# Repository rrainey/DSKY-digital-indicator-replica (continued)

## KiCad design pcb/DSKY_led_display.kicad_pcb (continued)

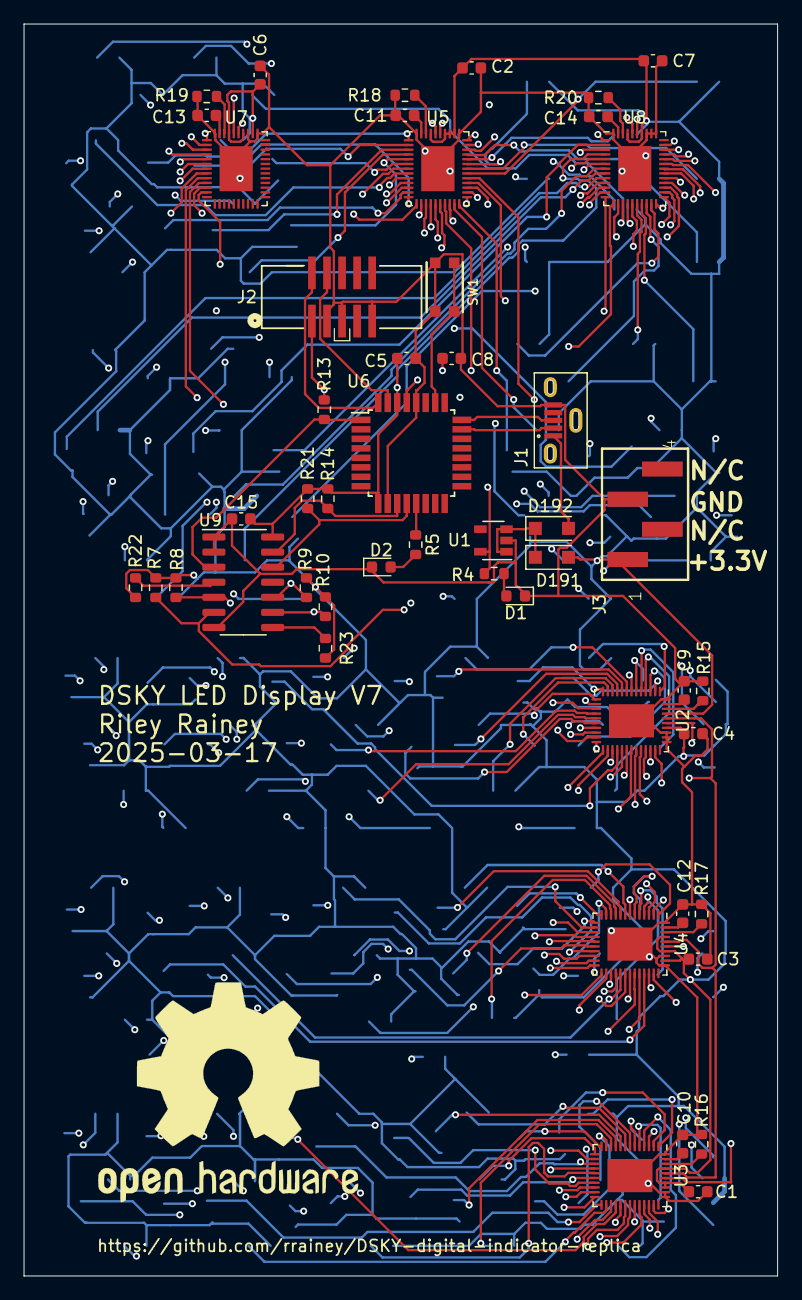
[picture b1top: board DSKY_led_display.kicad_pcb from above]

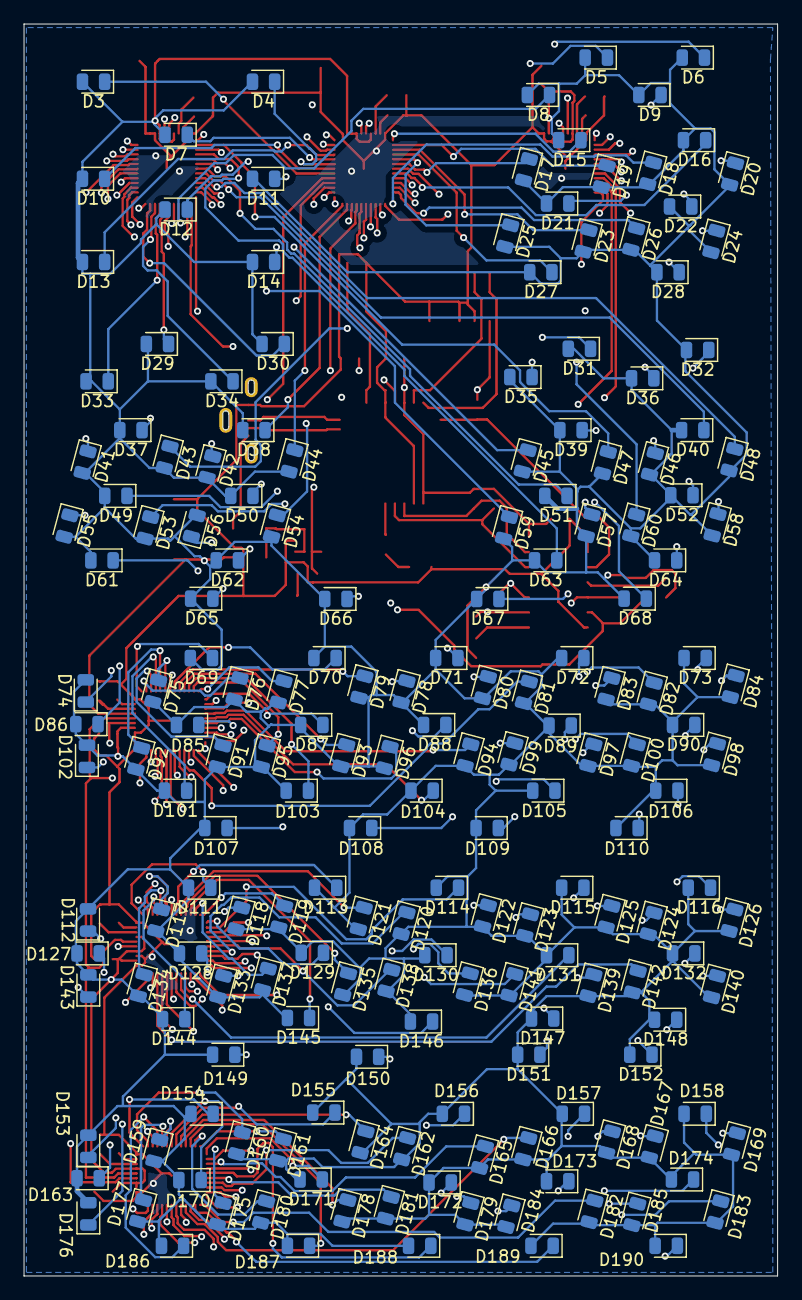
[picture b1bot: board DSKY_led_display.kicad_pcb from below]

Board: 4 copper layers, 63.5 x 105.5 mm, 237 parts (188 on the bottom side), 223 nets.

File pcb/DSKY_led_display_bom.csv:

Reference, Quantity, Value, Footprint, Datasheet, Description, Digi-Key_PN, Field4, Field5, Field6, Field7, Field8
C5 C15 ,2,10 uF,Capacitor_SMD:C_0603_1608Metric,~,CAP CER 10UF 25V X5R 0603,"	311-3494-1-ND",,,,,
C1 C2 C3 C4 C6 C7 C8 C9 C10 C11 C12 C13 C14 ,13,1 uF,Capacitor_SMD:C_0603_1608Metric,~,CAP CER 1UF 25V X7R 0603,"	399-C0603C105K3RAC7411CT-ND",,,,,
D1 ,1,PWR LED,LED_SMD:LED_0805_2012Metric,http://www.inolux-corp.com/datasheet/SMDLED/Mono%20Color%20T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,LTST-C190GKT ED GREEN CLEAR CHIP SMD,,,,,,
D191 D192 ,2,B0540W,Diode_SMD:D_SOD-123F,~,DIODE SCHOTTKY 40V 500MA SOD123,,,,,,
D2 ,1,red,LED_SMD:LED_0805_2012Metric,http://www.inolux-corp.com/datasheet/SMDLED/Mono%20Color%20T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,LTST-S270KRKT LED RED CLEAR CHIP SMD R/A,,,,,,
D3 D4 D5 D6 D7 D8 D9 D10 D11 D12 D13 D14 D15 D16 D17 D18 D19 D20 D21 D22 D23 D24 D25 D26 D27 D28 D29 D30 D31 D32 D33 D34 D35 D36 D37 D38 D39 D40 D41 D42 D43 D44 D45 D46 D47 D48 D49 D50 D51 D52 D53 D54 D55 D56 D57 D58 D59 D60 D61 D62 D63 D64 D65 D66 D67 D68 D69 D70 D71 D72 D73 D74 D75 D76 D77 D78 D79 D80 D81 D82 D83 D84 D85 D86 D87 D88 D89 D90 D91 D92 D93 D94 D95 D96 D97 D98 D99 D100 D101 D102 D103 D104 D105 D106 D107 D108 D109 D110 D111 D112 D113 D114 D115 D116 D117 D118 D119 D120 D121 D122 D123 D124 D125 D126 D127 D128 D129 D130 D131 D132 D133 D134 D135 D136 D137 D138 D139 D140 D141 D142 D143 D144 D145 D146 D147 D148 D149 D150 D151 D152 D153 D154 D155 D156 D157 D158 D159 D160 D161 D162 D163 D164 D165 D166 D167 D168 D169 D170 D171 D172 D173 D174 D175 D176 D177 D178 D179 D180 D181 D182 D183 D184 D185 D186 D187 D188 D189 D190 ,188,IN-S85ATG,LED_SMD:LED_0805_2012Metric,http://www.inolux-corp.com/datasheet/SMDLED/Mono%20Color%20T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,LED GREEN CLEAR 0805 SMD,"	1830-1079-1-ND",,,,,
J1 ,1,105133-0001,led-project:MOLEX_105133-0001,0.50 USD,CONN RCPT USB2.0 MICRO B SMD,"	WM9734CT-ND",None,105133-0001,Good,Molex,Conn Micro USB Type B RCP 5 POS 0.65mm Solder RA SMD 5 Terminal 1 Port Embossed T/R
J2 ,1,3221-10-0300-00-TR,led-project:3221-10-0300-00-TR,http://www.cnctech.us/pdfs/3221-XX-0300-00-TR_.pdf,"CONN HEADER SMD 10POS 1.27MM	",1175-2649-1-ND,,,,,
J3 ,1,TSM-104-01-L-SV,led-project:TSM-104-01-L-SV,,CONN HEADER SMD 4POS 2.54MM,SAM13287CT-ND,,,,,
R13 ,1,0K,Resistor_SMD:R_0603_1608Metric,~,RES SMD 1K OHM 5% 1/10W 0603,"	541-4.7KGCT-ND",,,,,
R15 R16 R17 R18 R19 R20 ,6,3.65K,Resistor_SMD:R_0603_1608Metric,~,"RES SMD 3.65K OHM 1% 1/3W 0603	",541-3.65KSCT-ND,,,,,
R4 R5 ,2,1.5K,Resistor_SMD:R_0603_1608Metric,~,"RES SMD 1.5K OHM 1% 1/10W 0603	",541-1781-1-ND,,,,,
R7 R8 R9 R10 R14 R21 R22 R23 ,8,1K,Resistor_SMD:R_0603_1608Metric,~,RES SMD 4.7K OHM 5% 1/10W 0603,"	541-4.7KGCT-ND",,,,,
SW1 ,1,KMR241NG,led-project:BTN_KMR2_4.6X2.8,,SWITCH TACTILE SPST-NO 0.05A 32V,,,,,,
U1 ,1,AP2204K-3.3,Package_TO_SOT_SMD:SOT-23-5,https://www.diodes.com/assets/Datasheets/AP2204.pdf,"IC REG LINEAR 3.3V 150MA SOT23-5	","	AP2204K-3.3TRG1DICT-ND",,,,,
U2 U3 U4 U5 U7 U8 ,6,LP5036,Package_DFN_QFN:VQFN-46-1EP_5x6mm_P0.4mm_EP2.8x3.8mm,http://www.ti.com/lit/ds/symlink/lp5036.pdf,LED DRIVER,"	296-LP5036RJVRCT-ND",,,,,
U6 ,1,ATSAMD21E18A-A,Package_QFP:TQFP-32_7x7mm_P0.8mm,http://ww1.microchip.com/downloads/en/DeviceDoc/SAM_D21_DA1_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,IC MCU 32BIT 256KB FLASH 32TQFP,ATSAMD21E18A-AU-ND,,,,,
U9 ,1,TCA9543ADR,Package_SO:SOIC-14_3.9x8.7mm_P1.27mm,,,,,,,,

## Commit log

2021-01-16 Import pcb folder
2021-01-16 Add README
2021-01-16 update .gitignore to allow CSV and XML files
2021-01-16 validate pcb project is accessible from a second dev box
2021-01-16 Add Fusion 360 assets
2021-01-16 update README to add image
2021-01-16 Starter image
2021-01-16 Swap out license file
2021-01-16 Add CC LICENSE.md
2021-01-17 Update README to include PCB status
2021-01-17 Update README notes on painting
2021-01-27 V2 pcb as-ordered for testing
2021-02-25 V3 board
2021-02-28 add prototype driver
2021-02-28 Add PCB fabrication notes
2021-03-01 General documentation updates
2021-07-20 starter updates for V3 board
2021-08-01 V4 board
    Version 4 of the PCB
2021-08-01 schematic PDF update
2021-08-18 intermediate version for V4 board
2021-08-19 improved V4 debugging info to USB serial logs
2021-08-20 added a segment-at-a-time test mode
2021-08-25 fix issue with leftmost digit segment - 'c' digit coded incorrectly
2021-08-25 driver cleanup
2021-08-26 some cleanup preparing for integration testing
2021-08-26 August status update
2021-09-20 make serial mode the default operation mode
2023-01-24 V4 PCB update
2023-01-25 Typo
2025-03-17 V7 PCB fixes placement of D56 LED -- it was reversed.
2025-03-17 V7 Gerbers and placement file - D56 placement was reversed in V6; corrected here
2025-03-17 Update owing to KiCad V7 being fussier about bus definitions
2025-03-17 Add some notes for V7 of the PCB
2025-03-17 Update PCB documentation
2025-03-17 Minor updates to the Arduino-based driver firmware.
2025-03-18 fix spelling error
2025-04-01 V6 and V7 PCB
2025-04-02 updated models including new light guide adapter
2025-04-02 add rendered
2025-04-03 update model and video
2025-04-05 Add SIngle Power Source mod notes
2025-04-06 update notes
